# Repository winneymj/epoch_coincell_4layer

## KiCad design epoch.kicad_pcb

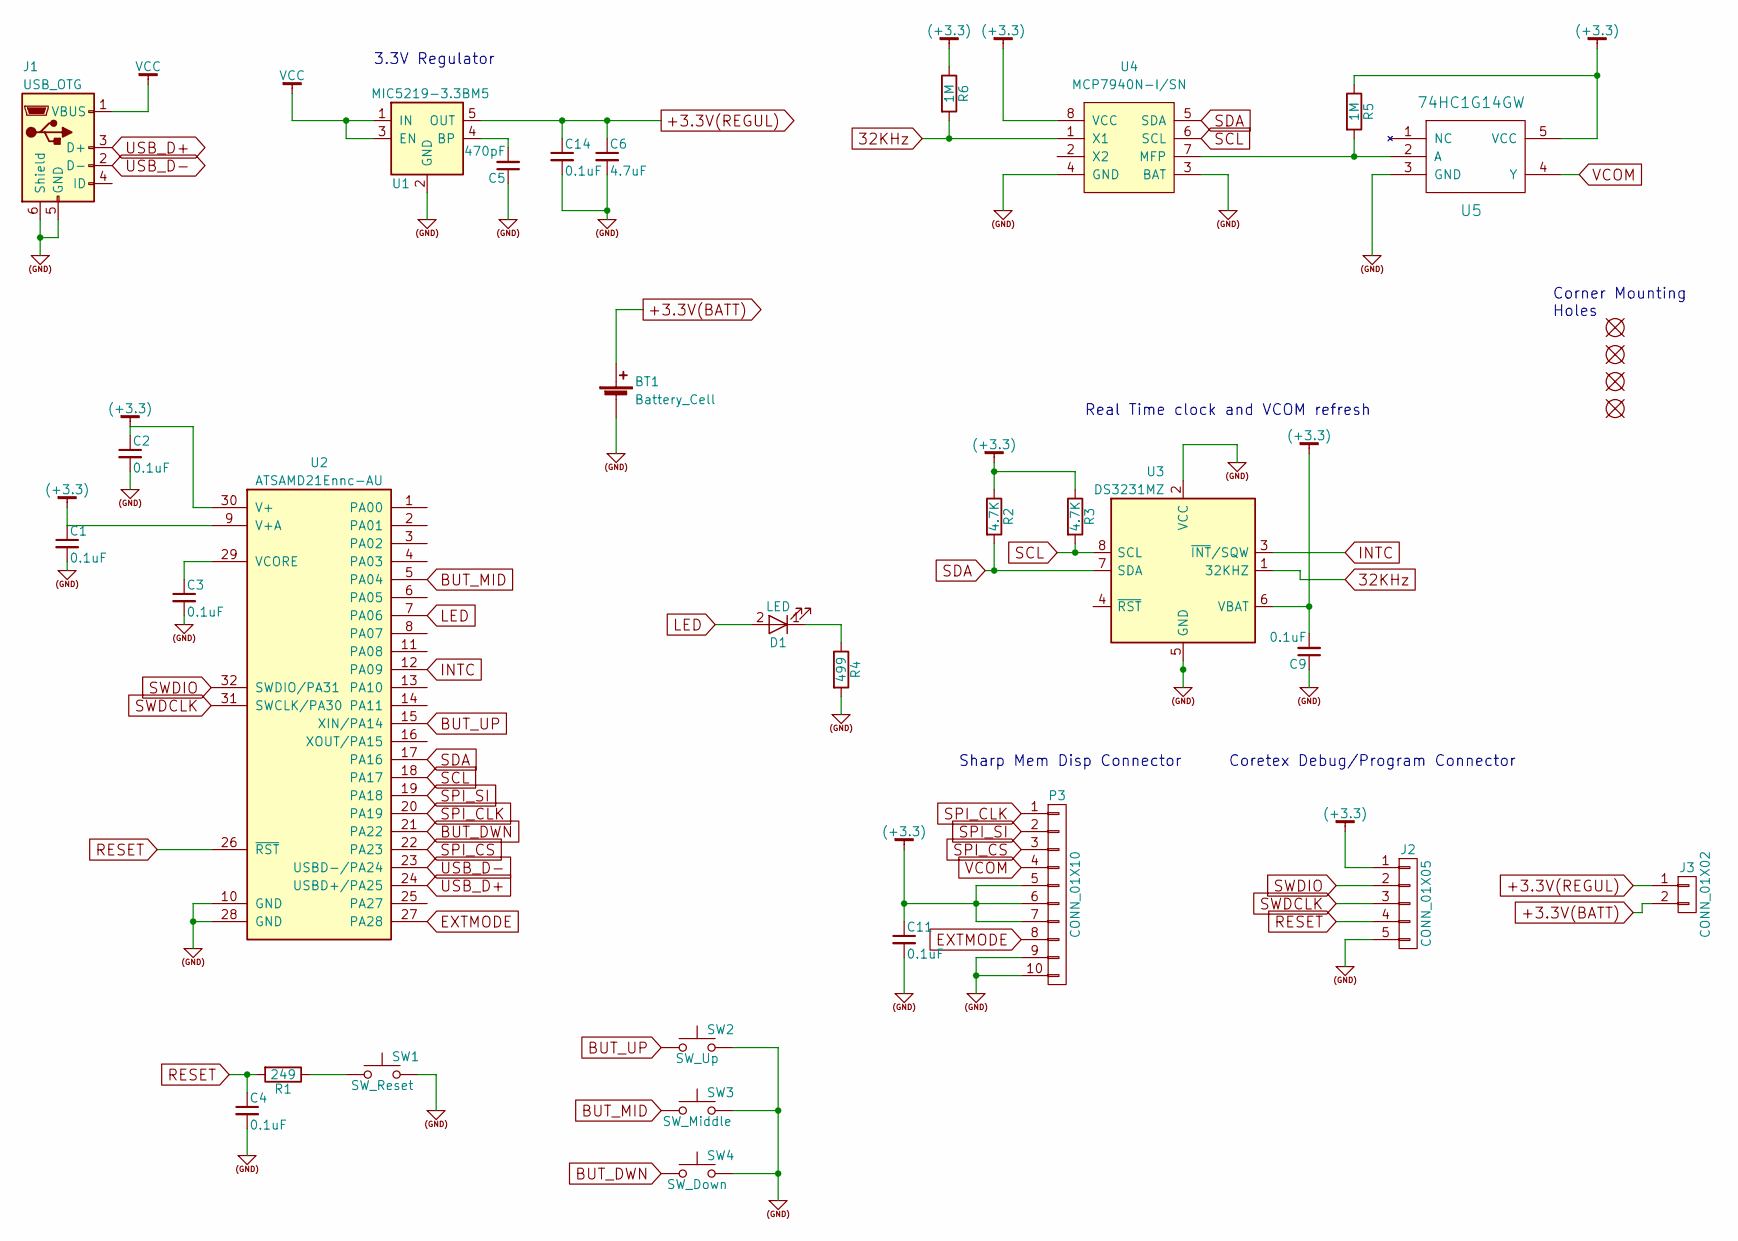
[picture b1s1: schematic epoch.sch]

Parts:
BT1: Battery_Cell; CR2032-001
C1, C2, C3, C4, C9, C11, C14: 0.1uF; C_0805_HandSoldering
C5: 470pF; C_0805_HandSoldering
C6: 4.7uF; C_0805_HandSoldering
D1: LED; LED_0805
J1: USB_OTG; USB-MICROB_LARGEPAD
J2: CONN_01X05; Pin_Header_Straight_1x05_Pitch1.27mm
J3: CONN_01X02; Pin_Header_Straight_1x02_Pitch1.27mm
P3: CONN_01X10; MOLEX_0.5MM_505278
R1: 249; R_0805_HandSoldering
R2, R3: 4.7K; R_0805_HandSoldering
R4: 499; R_0805_HandSoldering
R5, R6: 1M; R_0805_HandSoldering
SW1: SW_Reset; SW_SPST_B3U-3000P
SW2: SW_Up; SW_SPDT_EBAY_3PIN_VERT
SW3: SW_Middle; SW_SPDT_EBAY_3PIN_VERT
SW4: SW_Down; SW_SPDT_EBAY_3PIN_VERT
U1: MIC5219-3.3BM5; SOT-23-5
U2: ATSAMD21Ennc-AU; TQFP-32_7x7mm_Pitch0.8mm; MPN ATSAMD21Ennc-AU
U3: DS3231MZ; SOIC-8_3.9x4.9mm_Pitch1.27mm
U4: MCP7940N-I/SN; SOIC-8_3.9x4.9mm_Pitch1.27mm; MPN MCP7940N-I/SN
U5: 74HC1G14GW; SOT-353_SC-70-5_Handsoldering
U6, U7, U8, U9: MH2mm; MH2.1mm

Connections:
32KHz: R6.2, U3.1 (32KHZ), U4.1 (X1)
(+3.3): C1.1, C2.1, C9.2, C11.1, J2.1, P3.5, P3.6, P3.7, R2.1, R3.1, R5.1, R6.1, U2.9 (V+A), U2.30 (V+), U3.6 (VBAT), U4.8 (VCC), U5.5 (VCC)
(GND): BT1.2 (-), C1.2, C2.2, C3.2, C4.2, C5.1, C6.2, C9.1, C11.2, C14.2, J1.5 (GND), J1.6 (Shield), J2.5, P3.9, P3.10, R4.2, SW1.2, SW2.2, SW3.2, SW4.2, U1.2 (GND), U2.10 (GND), U2.28 (GND), U3.2 (VCC), U3.5 (GND), U4.3 (BAT), U4.4 (GND), U5.3 (GND)
+3.3V(BATT): BT1.1 (+), J3.2
+3.3V(REGUL): C6.1, C14.1, J3.1, U1.5 (OUT)
BUT_DWN: SW4.1, U2.21 (PA22)
BUT_MID: SW3.1, U2.5 (PA04)
BUT_UP: SW2.1, U2.15 (XIN/PA14)
EXTMODE: P3.8, U2.27 (PA28)
INTC: U2.12 (PA09), U3.3 (~INT~/SQW)
LED: D1.2 (A), U2.7 (PA06)
unnamed: C3.1, U2.29 (VCORE)
unnamed: C5.2, U1.4 (BP)
unnamed: D1.1 (K), R4.1
unnamed: R1.1, SW1.1
unnamed: R5.2, U4.7 (MFP), U5.2 (A)
RESET: C4.1, J2.4, R1.2, U2.26 (~RST)
SCL: R3.2, U2.18 (PA17), U3.8 (SCL), U4.6 (SCL)
SDA: R2.2, U2.17 (PA16), U3.7 (SDA), U4.5 (SDA)
SPI_CLK: P3.1, U2.20 (PA19)
SPI_CS: P3.3, U2.22 (PA23)
SPI_SI: P3.2, U2.19 (PA18)
SWDCLK: J2.3, U2.31 (SWCLK/PA30)
SWDIO: J2.2, U2.32 (SWDIO/PA31)
USB_D+: J1.3 (D+), U2.24 (USBD+/PA25)
USB_D-: J1.2 (D-), U2.23 (USBD-/PA24)
VCC: J1.1 (VBUS), U1.1 (IN), U1.3 (EN)
VCOM: P3.4, U5.4 (Y)

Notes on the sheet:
Coretex Debug/Program Connector
3.3V Regulator
Sharp Mem Disp Connector
Real Time clock and VCOM refresh
Corner Mounting Holes

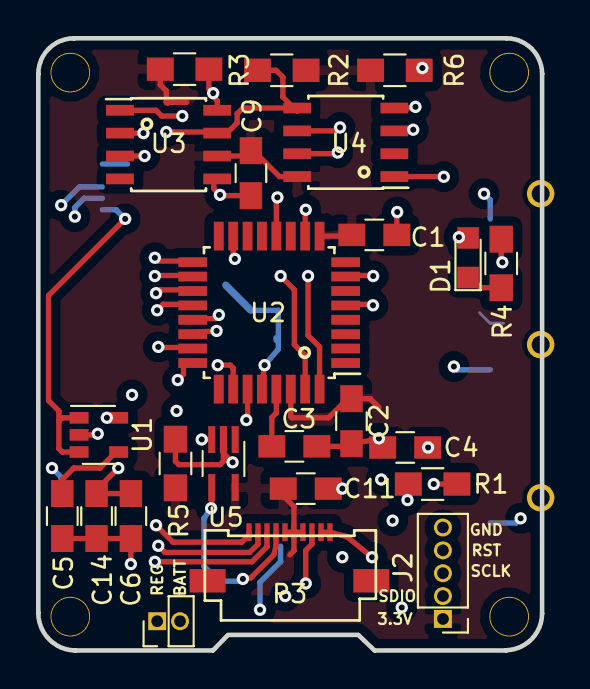
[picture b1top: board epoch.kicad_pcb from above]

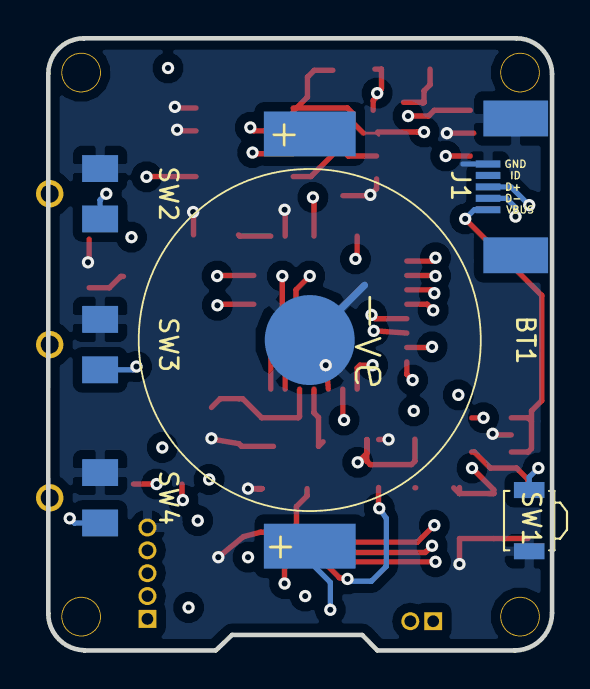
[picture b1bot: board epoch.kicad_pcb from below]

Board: 4 copper layers, 28.0 x 34.0 mm, 34 parts (6 on the bottom side), 28 nets.

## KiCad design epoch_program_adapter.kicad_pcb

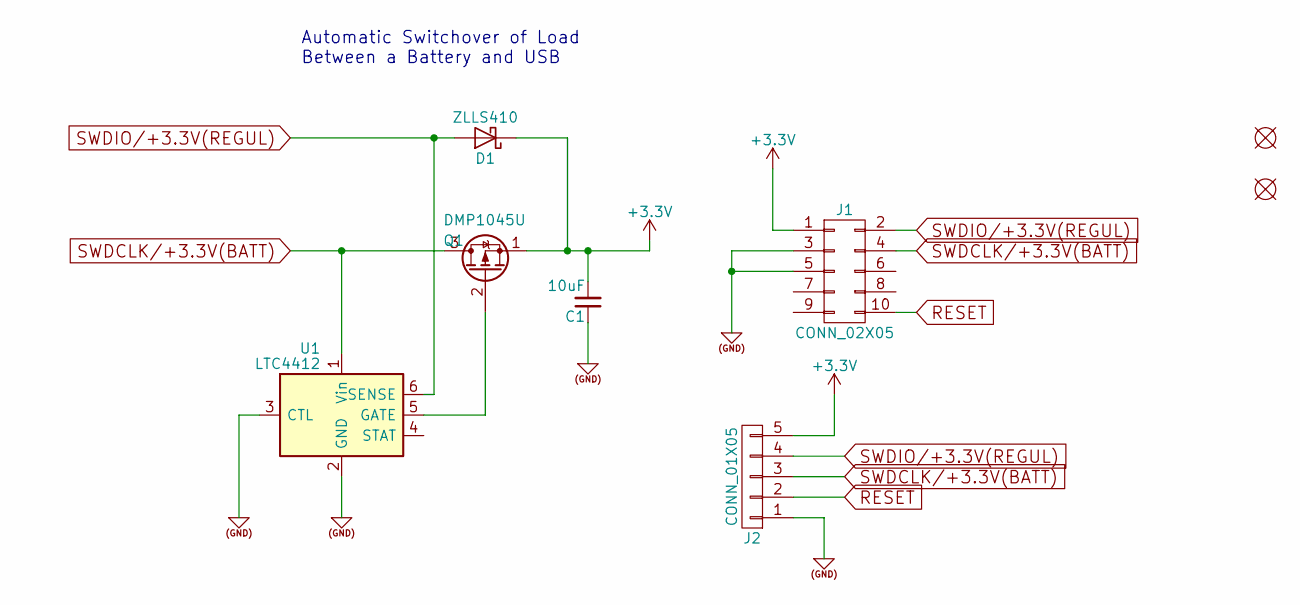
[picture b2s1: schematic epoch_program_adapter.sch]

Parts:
C1: 10uF; C_0805_HandSoldering
D1: ZLLS410; D_SOD-323_HandSoldering
H1, H2: MH2mm; MH2.1mm
J1: CONN_02X05; Pin_Header_Straight_2x05_Pitch1.27mm
J2: CONN_01X05; Pin_Header_Straight_1x05_Pitch1.27mm
Q1: DMP1045U; TSOT-23_HandSoldering
U1: LTC4412; SOT-23-6_Handsoldering

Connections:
(GND): C1.1, J1.3, J1.5, J2.1, U1.2 (GND), U1.3 (CTL)
+3V3: C1.2, D1.1 (K), J1.1, J2.5, Q1.1 (S)
unnamed: Q1.2 (G), U1.5 (GATE)
RESET: J1.10, J2.2
SWDCLK/+3.3V(BATT): J1.4, J2.3, Q1.3 (D), U1.1 (Vin)
SWDIO/+3.3V(REGUL): D1.2 (A), J1.2, J2.4, U1.6 (SENSE)

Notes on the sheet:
Automatic Switchover of Load Between a Battery and USB

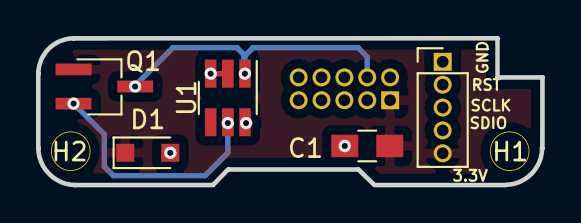
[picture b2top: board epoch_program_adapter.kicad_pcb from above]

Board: 4 copper layers, 28.0 x 8.2 mm, 8 parts (1 on the bottom side), 6 nets.

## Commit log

2017-05-10 Final connections
2017-05-12 New buttons
2017-05-12 Closed
2017-05-13 Update all buttons and re-route
2017-05-13 final. Sent to manufacturer
2017-08-03 Correct interrupt connections to pins that actually support interrupts
2017-08-22 New version with crystal removed and 32Khz output into XTA of 2nd RTC
2017-09-10 Add Automatic Switchover of Load Between a Battery
2017-09-10 Add drills back to PCB...Note this PCB does not include the battery protection switch which is shown in the schematic.
    Not sure I have the PBC space to do this. Maybe do a separate board. Not sure.
2017-09-10 Revert "Add drills back to PCB...Note this PCB does not include the battery protection switch which is shown in the schematic."
    This reverts commit 0a23e0f0d40f65d1b6f1174f50c74f54a2cdcd00.
2017-09-10 Revert "Add Automatic Switchover of Load Between a Battery"
    This reverts commit 427980174dfe5bb42044178e8a82d6b50698685d.
2017-09-10 Add back corner drill holes
2017-09-10 correct the routing after adding drills back
2017-09-22 Update drills
2017-09-23 Use same connector for hotswap
2017-09-23 Implement new schematic for adapter board
2017-09-24 Increase drill size to 2.1. Rework daughter board
2017-09-26 V2.0 - Manufactured Board and Adapter
2018-02-05 update for RTC battery grounding and clock pull-up increased to 1M to reduce power consumption
2018-02-16 Update PCB to move battery and USB
2018-03-05 Move reference text
2018-03-05 Backup
